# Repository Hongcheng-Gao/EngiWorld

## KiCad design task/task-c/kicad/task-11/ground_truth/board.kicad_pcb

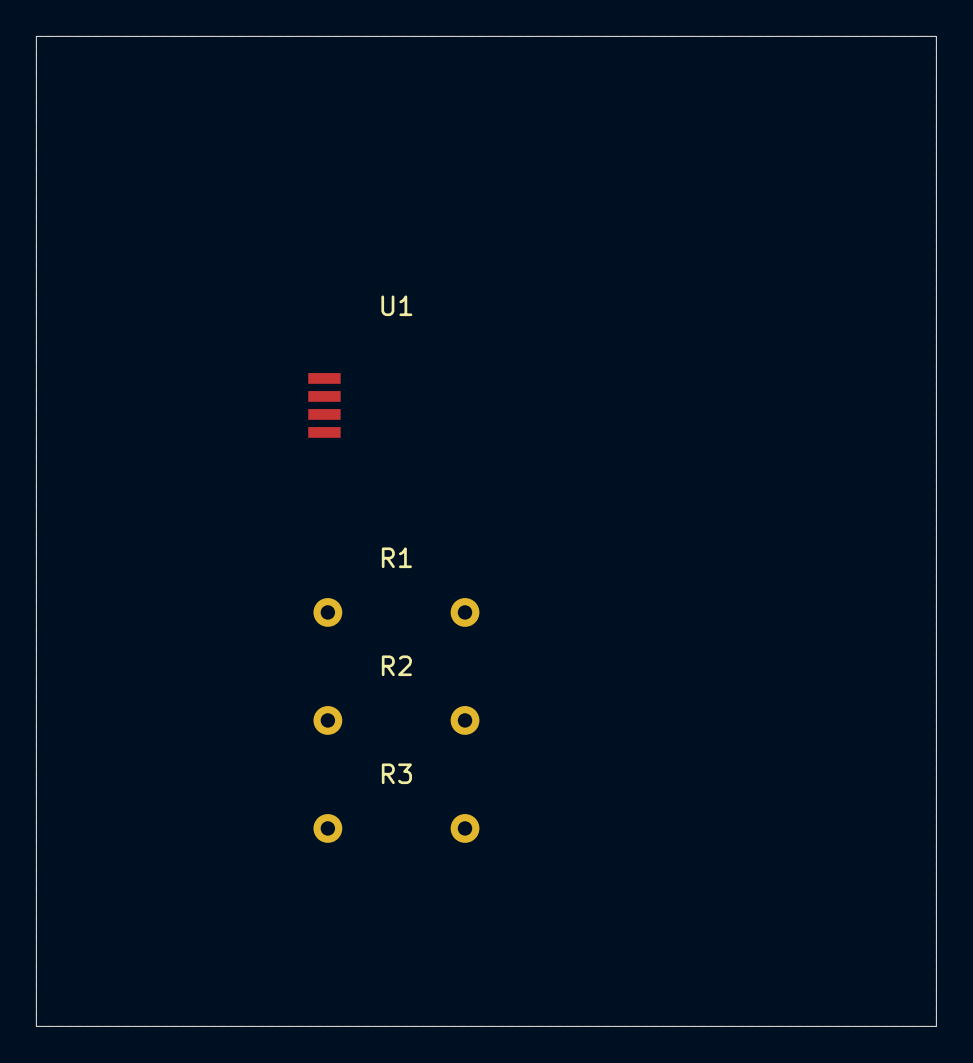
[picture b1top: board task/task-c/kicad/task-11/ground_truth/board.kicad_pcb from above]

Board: 2 copper layers, 50.0 x 55.0 mm, 4 parts (0 on the bottom side), 4 nets, no tracks yet.

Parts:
R1, R2: 10k; R_Axial_DIN0204_L3.6mm_D1.6mm_P7.62mm_Horizontal
R3: DNP; R_Axial_DIN0204_L3.6mm_D1.6mm_P7.62mm_Horizontal
U1: IC; LQFP-32_7x7mm_P0.8mm

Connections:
DNC_NET: R3.1, R3.2
GND: R1.2, R2.2, U1.4
SIG_A: R1.1, U1.3
VCC: U1.1, U1.2

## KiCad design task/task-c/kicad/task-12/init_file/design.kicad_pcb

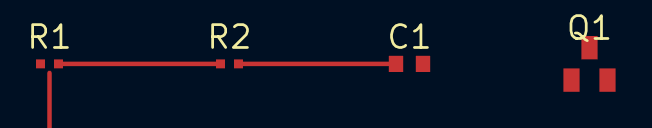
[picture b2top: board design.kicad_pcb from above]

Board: 2 copper layers, 4 parts (0 on the bottom side), 3 nets.

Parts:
C1: 100nF; C_0603
Q1: 2N7002; SOT-23
R1: 10k; R_0402
R2: 22k; R_0402

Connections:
GND: C1.2, Q1.1, R1.2
SIG_A: Q1.2, R2.2
VCC: C1.1, Q1.3, R1.1, R2.1

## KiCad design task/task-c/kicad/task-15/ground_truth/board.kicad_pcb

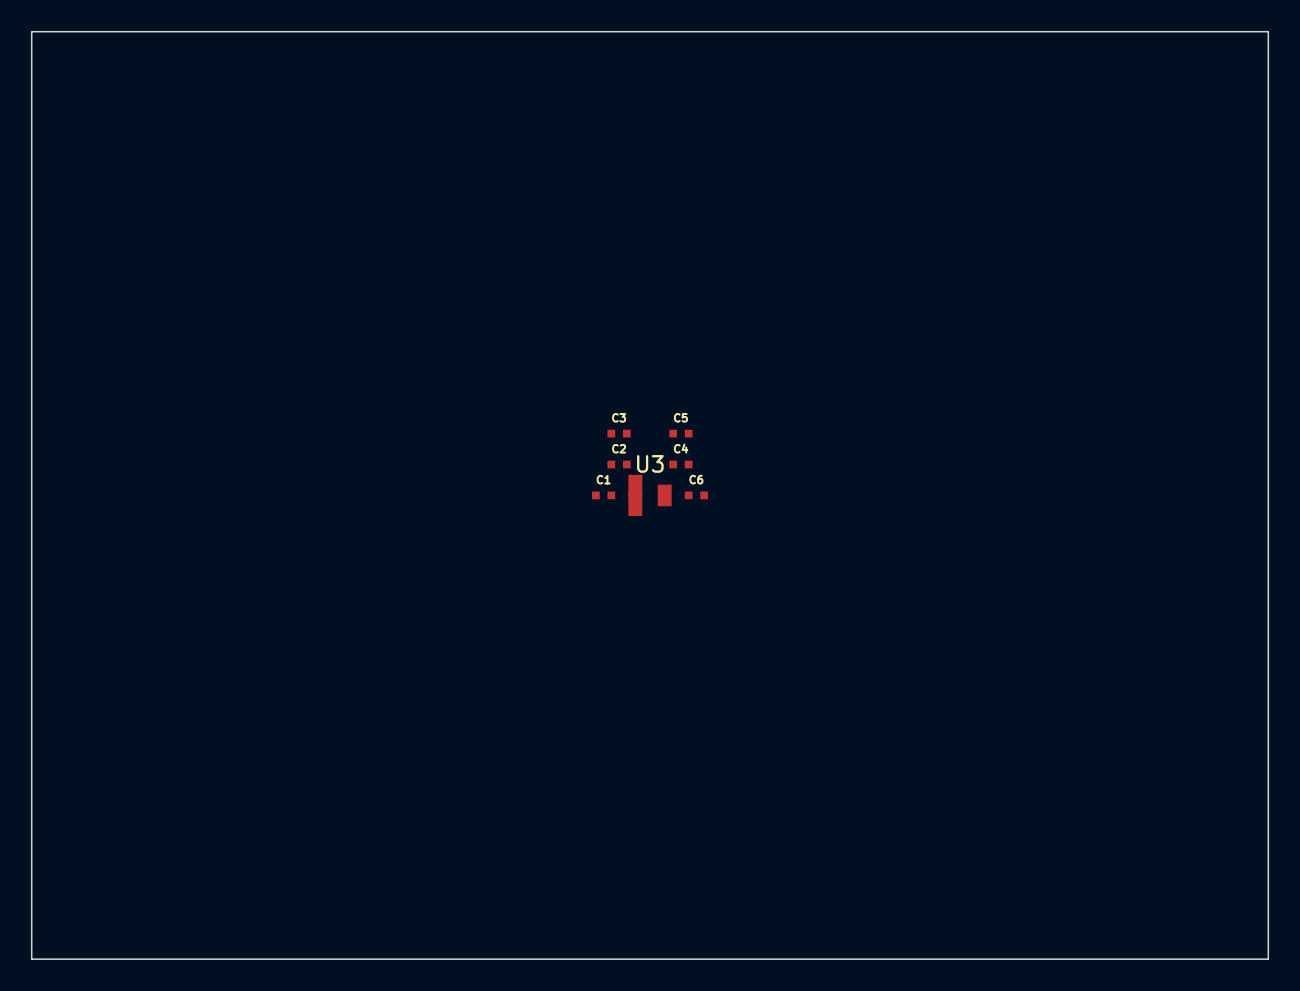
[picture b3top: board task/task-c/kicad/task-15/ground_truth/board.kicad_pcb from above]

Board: 2 copper layers, 80.0 x 60.0 mm, 7 parts (0 on the bottom side), 2 nets, no tracks yet.

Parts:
C1: 100nF; C_0402
C2, C3, C4: 10uF; C_0402
C5, C6: 10nF; C_0402
U3: MCU; SOT-23

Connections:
3V3: C1.1, C2.1, C3.1, C4.1, C5.1, C6.1, U3.1, U3.3
GND: C1.2, C2.2, C3.2, C4.2, C5.2, C6.2, U3.2

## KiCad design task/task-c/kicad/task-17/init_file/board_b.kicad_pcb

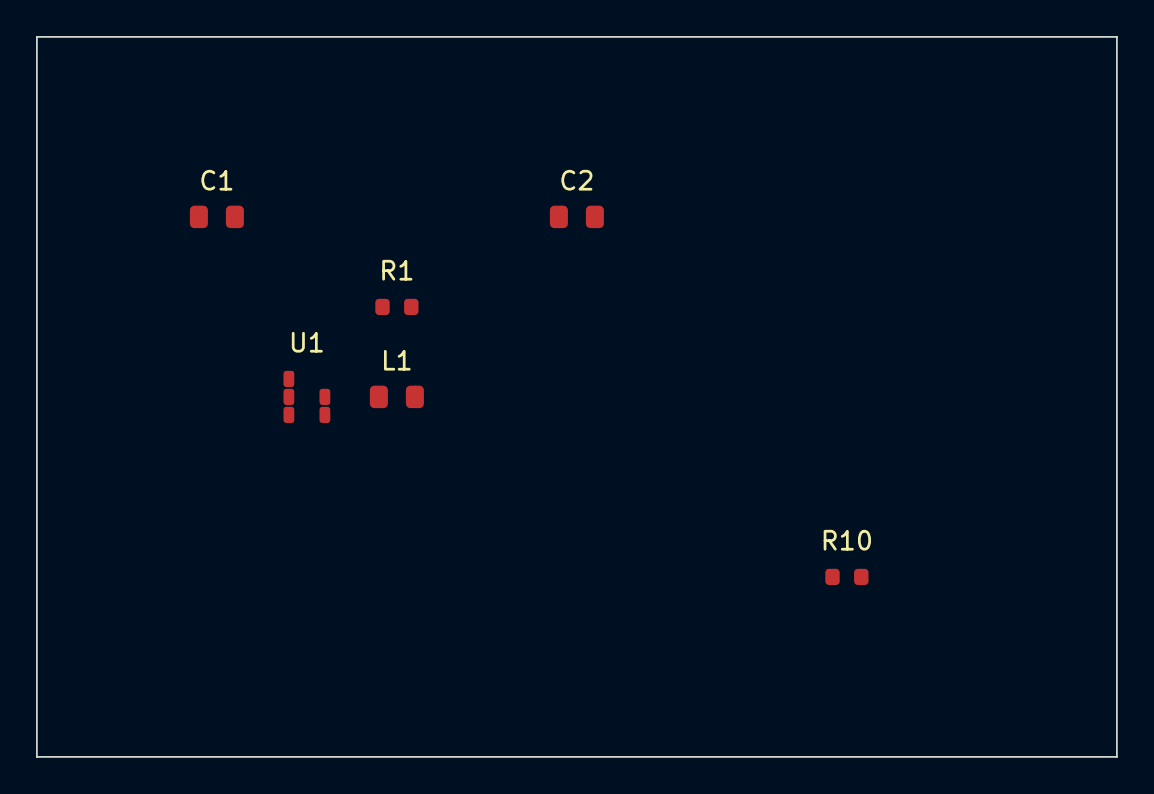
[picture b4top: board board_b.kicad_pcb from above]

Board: 2 copper layers, 60.0 x 40.0 mm, 6 parts (0 on the bottom side), 5 nets, no tracks yet.

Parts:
C1: 4u7; C_0805
C2: 22uF; C_0805
L1: 4u7; L_0805
R1: 10k; R_0603
R10: 1k; R_0603
U1: LM3671; SOT-23-5

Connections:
FBK: R1.2, U1.4
GND: C1.2, C2.2, R10.2, U1.2
SW: L1.1, U1.1
VIN: C1.1, U1.3, U1.5
VOUT: C2.1, L1.2, R1.1, R10.1

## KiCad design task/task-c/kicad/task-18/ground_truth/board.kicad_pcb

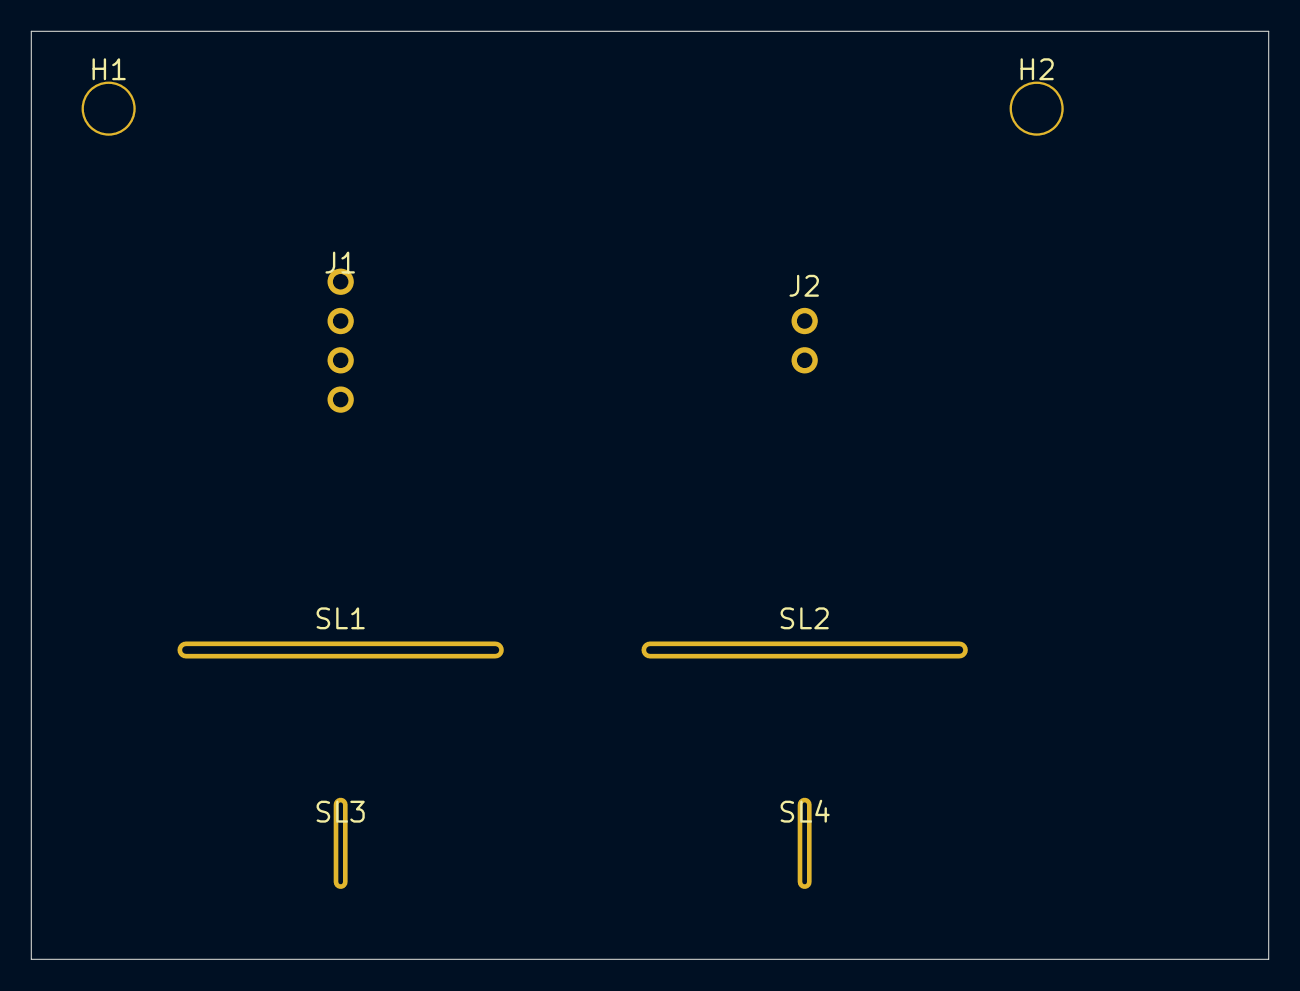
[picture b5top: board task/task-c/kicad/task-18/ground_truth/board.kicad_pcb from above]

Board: 2 copper layers, 80.0 x 60.0 mm, 8 parts (0 on the bottom side), 2 nets, no tracks yet.

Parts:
H1, H2: MH; MountingHole_3.2mm_M3
J1: HDR_4; PinHeader_1x04_P2.54mm_Vertical
J2: HDR_2; PinHeader_1x02_P2.54mm_Vertical
SL1, SL2: SLOT; PlatedSlot_20x0p5
SL3, SL4: SLOT; PlatedSlot_5x0p3

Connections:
GND: J1.1, J1.3, J2.1
VCC: J1.2, J1.4, J2.2
